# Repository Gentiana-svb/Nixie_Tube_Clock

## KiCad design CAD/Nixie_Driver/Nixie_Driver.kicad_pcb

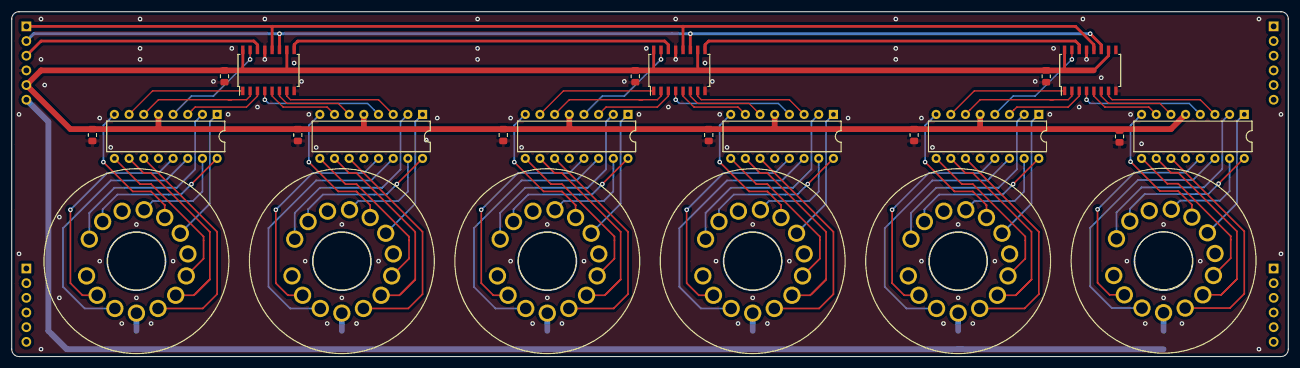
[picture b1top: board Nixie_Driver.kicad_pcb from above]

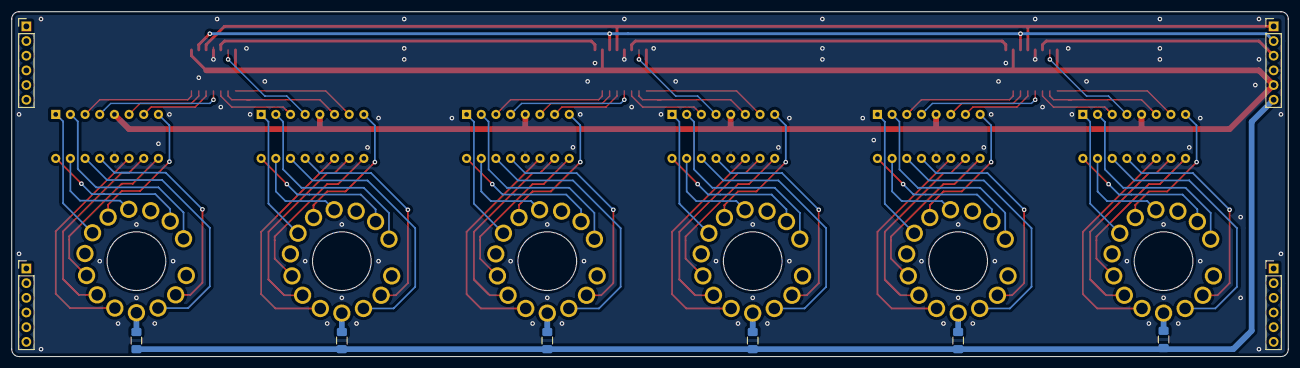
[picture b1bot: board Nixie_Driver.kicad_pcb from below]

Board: 2 copper layers, 221.0 x 59.7 mm, 34 parts (10 on the bottom side), 98 nets.

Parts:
C1, C2, C3, C4, C5, C6, C7, C8, C9: 0.1u; C_0805_2012Metric_Pad1.15x1.40mm_HandSolder
J1, J2, J3, J4: Conn_01x06; PinHeader_1x06_P2.54mm_Vertical
R1, R2, R3, R4, R5, R6: 10k; R_1206_3216Metric_Pad1.42x1.75mm_HandSolder
U1, U2, U3: 74HC595; SOIC-16W_5.3x10.2mm_P1.27mm
U4, U5, U6, U10, U11, U12: 74141; DIP-16_W7.62mm
U7, U8, U9, U13, U14, U15: IN-18

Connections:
+5V: C1.1, C2.1, C3.1, C4.1, C5.1, C6.1, C7.1, C8.1, C9.1, J1.5, U1.10, U1.16, U2.10, U2.16, U3.10, U3.16, U4.5, U5.5, U6.5, U10.5, U11.5, U12.5
+48V: J1.6, R1.1, R2.1, R3.1, R4.1, R5.1, R6.1
/HH1: U1.3, U4.3
/HH2: U1.2, U4.6
/HH4: U1.1, U4.7
/HH8: U1.15, U4.4
/HL1: U1.7, U5.3
/HL2: U1.6, U5.6
/HL4: U1.5, U5.7
/HL8: U1.4, U5.4
/MH1: U2.3, U6.3
/MH2: U2.2, U6.6
/MH4: U2.1, U6.7
/MH8: U2.15, U6.4
/ML1: U2.7, U10.3
/ML2: U2.6, U10.6
/ML4: U2.5, U10.7
/ML8: U2.4, U10.4
/RCK: J1.1, U1.12, U2.12, U3.12
/SCK: J1.2, U1.11, U2.11, U3.11
/SH1: U3.3, U11.3
/SH2: U3.2, U11.6
/SH4: U3.1, U11.7
/SH8: U3.15, U11.4
/SL1: U3.7, U12.3
/SL2: U3.6, U12.6
/SL4: U3.5, U12.7
/SL8: U3.4, U12.4
GND: C1.2, C2.2, C3.2, C4.2, C5.2, C6.2, C7.2, C8.2, C9.2, J1.4, U1.8, U1.13, U2.8, U2.13, U3.8, U3.13, U4.12, U5.12, U6.12, U10.12, U11.12, U12.12
unnamed: J1.3, U1.14
unnamed: R1.2, U7.4
unnamed: R2.2, U8.4
unnamed: R3.2, U9.4
unnamed: R4.2, U13.4
unnamed: R5.2, U14.4
unnamed: R6.2, U15.4
unnamed: U1.9, U2.14
unnamed: U2.9, U3.14
unnamed: U4.1, U7.9
unnamed: U4.2, U7.14
unnamed: U4.8, U7.10
unnamed: U4.9, U7.7
unnamed: U4.10, U7.6
unnamed: U4.11, U7.5
unnamed: U4.13, U7.2
unnamed: U4.14, U7.3
unnamed: U4.15, U7.11
unnamed: U4.16, U7.13
unnamed: U5.1, U8.9
unnamed: U5.2, U8.14
unnamed: U5.8, U8.10
unnamed: U5.9, U8.7
unnamed: U5.10, U8.6
unnamed: U5.11, U8.5
unnamed: U5.13, U8.2
unnamed: U5.14, U8.3
unnamed: U5.15, U8.11
unnamed: U5.16, U8.13
unnamed: U6.1, U9.9
unnamed: U6.2, U9.14
unnamed: U6.8, U9.10
unnamed: U6.9, U9.7
unnamed: U6.10, U9.6
unnamed: U6.11, U9.5
unnamed: U6.13, U9.2
unnamed: U6.14, U9.3
unnamed: U6.15, U9.11
unnamed: U6.16, U9.13
unnamed: U10.1, U13.9
unnamed: U10.2, U13.14
unnamed: U10.8, U13.10
unnamed: U10.9, U13.7
unnamed: U10.10, U13.6
unnamed: U10.11, U13.5
unnamed: U10.13, U13.2
unnamed: U10.14, U13.3
unnamed: U10.15, U13.11
unnamed: U10.16, U13.13
unnamed: U11.1, U14.9
unnamed: U11.2, U14.14
unnamed: U11.8, U14.10
unnamed: U11.9, U14.7
unnamed: U11.10, U14.6
unnamed: U11.11, U14.5
unnamed: U11.13, U14.2
unnamed: U11.14, U14.3
unnamed: U11.15, U14.11
unnamed: U11.16, U14.13
unnamed: U12.1, U15.9
unnamed: U12.2, U15.14
unnamed: U12.8, U15.10
unnamed: U12.9, U15.7
unnamed: U12.10, U15.6
unnamed: U12.11, U15.5
unnamed: U12.13, U15.2
unnamed: U12.14, U15.3
unnamed: U12.15, U15.11
unnamed: U12.16, U15.13

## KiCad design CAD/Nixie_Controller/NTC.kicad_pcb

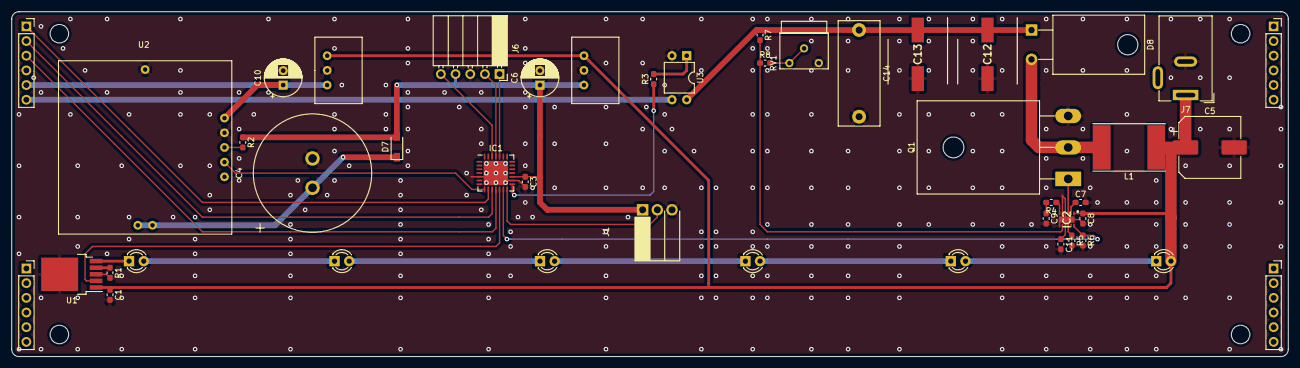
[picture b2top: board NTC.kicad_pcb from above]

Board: 2 copper layers, 221.0 x 59.7 mm, 46 parts (0 on the bottom side), 36 nets.

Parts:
C1, C3: 0.1u; C_0603_1608Metric_Pad1.05x0.95mm_HandSolder
C4: 1.5F; EDLC
C5: 100u; CP_Elec_10x10.5
C6, C10: 100u; CP_Radial_D6.3mm_P2.50mm
C7: 1u; C_0603_1608Metric_Pad1.05x0.95mm_HandSolder
C8: 10u; C_0603_1608Metric_Pad1.05x0.95mm_HandSolder
C9: 0.022u; C_0603_1608Metric_Pad1.05x0.95mm_HandSolder
C11: 0.22u; C_0603_1608Metric_Pad1.05x0.95mm_HandSolder
C12, C13: ULR2G8R2MNL1GS; CAPAE1030X1100N
C14: 0.1u; C_Rect_L18.0mm_W7.0mm_P15.00mm_FKS3_FKP3
D1, D2, D3, D4, D5, D6: LED; LED_D3.0mm_Clear
D7: SS2040FL; SOD-123FL
D8: SCS206AG; TO-220-2_Horizontal_TabDown
IC1: PIC18F27Q10T-I_ML; QFN-28-1EP_6x6mm_P0.65mm_EP4.25x4.25mm
IC2: LM51551DSSR; SON50P200X300X80-13N
J1: SB412A
J2, J3, J4, J5: Conn_01x06; PinSocket_1x06_P2.54mm_Vertical
J6: ICSP; PinSocket_1x05_P2.54mm_Horizontal
J7: Barrel_Jack_Switch; BarrelJack_Wuerth_6941xx301002
L1: 22u; L_Taiyo-Yuden_NR-80xx_HandSoldering
Q1: TK31N60X; TO-247-3_Horizontal_TabDown
R1: 20; R_0603_1608Metric_Pad1.05x0.95mm_HandSolder
R2, R6, R8: 10k; R_0603_1608Metric_Pad1.05x0.95mm_HandSolder
R3: 300; R_0603_1608Metric_Pad1.05x0.95mm_HandSolder
R4: 12k; R_0603_1608Metric_Pad1.05x0.95mm_HandSolder
R5: 43k; R_0603_1608Metric_Pad1.05x0.95mm_HandSolder
R7: 2M; R_0603_1608Metric_Pad1.05x0.95mm_HandSolder
RV1: 4.7k; Potentiometer_Bourns_3339W_Horizontal
U1: NJW4617; TO-252-5_TabPin3
U2: AE-GPS
U3: TLP627; DIP-4_W7.62mm
U4: M78AR033-1; M78AR-1
U5: M78AR05-1; M78AR-1

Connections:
+3V3: C3.1, C6.1, D7.2, IC1.17, J1.1, J6.4, R2.1, U4.3
+5V: C10.1, J5.5, U2.1, U5.3
+24V: C1.1, C5.1, C8.1, D1.2, IC2.1, J7.1, L1.1, U1.1, U4.1, U5.1
+200V: C12.1, C13.1, C14.1, D8.1, R7.1, U3.4
/BRT: IC1.15, R3.1
/HV: J5.6, U3.3
/LED: IC1.12, U1.2
/MCLR: IC1.26, J6.5
/PGC: IC1.24, J6.1
/PGD: IC1.25, J6.2
/Pyro: IC1.14, J1.2
/RCK: IC1.9, J5.1
/RX: IC1.8, U2.4
/SCK: IC1.10, J5.2
/SER: IC1.11, J5.3
/power/GATE: IC2.3, Q1.1
EN: IC1.13, IC2.12, R6.1
GND: C1.2, C3.2, C4.2, C5.2, C6.2, C7.2, C8.2, C9.2, C10.2, C11.2, C12.2, C13.2, C14.2, IC1.5, IC1.16, IC1.29, IC2.4, IC2.5, IC2.7, IC2.13, J1.3, J5.4, J6.3, J7.2, Q1.3, R1.2, R5.2, R6.2, RV1.3, U1.3, U2.2, U2.8, U3.2, U4.2, U5.2
unnamed: C4.1, D7.1, U2.6, U2.7
unnamed: C7.1, IC2.2
unnamed: C9.1, R4.2
unnamed: C11.1, IC2.9
unnamed: D1.1, D2.2
unnamed: D2.1, D3.2
unnamed: D3.1, D4.2
unnamed: D4.1, D5.2
unnamed: D5.1, D6.2
unnamed: D6.1, U1.5
unnamed: D8.2, L1.2, Q1.2
unnamed: IC2.6, R4.1
unnamed: IC2.8, R7.2, R8.1
unnamed: IC2.10, R5.1
unnamed: R1.1, U1.4
unnamed: R2.2, U2.3
unnamed: R3.2, U3.1
unnamed: R8.2, RV1.1, RV1.2

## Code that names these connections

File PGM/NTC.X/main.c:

// Nixie Tube Clock Controll Program
// MCU      : PIC18F27Q10
// Compiler : XC8 v2.32
// Date     : 3/27/2021

#include "config.h"
#include "library/UART/UART.h"
#include <stdint.h>
#include <string.h>
#include <xc.h>

// PORT Define
#define RX   RC0
#define RCK  LATC1
#define SCK  LATC2
#define SI   LATC3
#define LED  LATC4
#define EN   LATC5
#define PYRO RC6
#define BRT  LATC7

// DGM Effect
#define DGM_TIME  3.5 // sec
#define DGM_START (DGM_TIME * 100) / 5
#define DGM_INT   (100 - DGM_START) / 5

// Global
_Bool g_t0_f;
_Bool dgm_f;
uint32_t g_time;

// RTC Receive
void RTC_Read(uint8_t data);

// Data Conversion
uint32_t Convert_data(uint32_t data);
uint32_t DGM_Effect(uint32_t time, uint8_t val);

// Device Control
void NTC_Write(uint32_t data);
void Duty_Control();
void IC595_Write(uint24_t data);

// Peripheral Control
void Set_PWM_Duty(uint8_t ch, int16_t duty);
_Bool T0_int(int16_t val);
_Bool T0_int2(int16_t val);

// Initialize
void init()
{
    // OSC
    OSCCON1 = 0x60;
    OSCFRQ = 0x08;

    // I/O
    TRISA = 0x00;
    TRISB = 0x00;
    TRISC = 0x41;

    // A/D
    ANSELA = 0x00;
    ANSELB = 0x00;
    ANSELC = 0x00;

    // Timer0
    T0CON0 = 0x90;
    T0CON1 = 0xd0; // 500kHz
    TMR0IE = 1;

    // Timer2
    T2CLKCON = 0x01; // Clock source is Fosc/4
    T2PR = 0xfe;     // Maximum Duty Resolution
    T2CON = 0xf0;    // Timer2 enable, Pre scaler 1:128, Post scaler 1:1

    // PWM3
    PWM3CON = 0x80;            // PWM enable
    CCPTMRSbits.P3TSEL = 0x01; // PWM3 based Timer2
    Set_PWM_Duty(3, 0);

    // PWM4
    PWM4CON = 0x80;            // PWM enable
    CCPTMRSbits.P4TSEL = 0x01; // PWM4 based Timer2
    Set_PWM_Duty(4, 0);

    // PPS unlock
    PPSLOCK = 0x55;
    PPSLOCK = 0xAA;
    PPSLOCK = 0x00;

    // PPS
    RX1PPS = 0x10; // RC0 = RX1
    RC4PPS = 0x07; // RC4 = PWM3
    RC7PPS = 0x08; // RC7 = PWM4

    // PPS lock
    PPSLOCK = 0x55;
    PPSLOCK = 0xAA;
    PPSLOCK = 0x00;

    // Interrupts
    ei();
    PEIE = 1;

    // UART
    UART_Init(9600);
}

// Main
void main()
{
    uint8_t cnt = 0;
    uint8_t val = 0;

    init();

    while (1) {
        if (T0_int(2)) {
            Duty_Control();
        }

        if (EN) {
            if (T0_int2(50)) {
                if (dgm_f) {
                    cnt++;

                    if (cnt < DGM_START) {
                        val = 6;
                    }
                    else if (cnt < (DGM_START + DGM_INT * 1)) {
                        val = 5;
                    }
                    else if (cnt < (DGM_START + DGM_INT * 2)) {
                        val = 4;
                    }
                    else if (cnt < (DGM_START + DGM_INT * 3)) {
                        val = 3;
                    }
                    else if (cnt < (DGM_START + DGM_INT * 4)) {
                        val = 2;
                    }
                    else if (cnt < (DGM_START + DGM_INT * 5)) {
                        val = 1;
                    }
                    else {
                        val = 0;
                        dgm_f = 0;
                        cnt = 0;
                    }

                    NTC_Write(DGM_Effect(g_time, val));
                }
                else {
                    NTC_Write(g_time);
                }
            }
        }
        else {
            if (dgm_f) {
                dgm_f = 0;
            }
        }
    }
}

// Interupts
void __interrupt() isr()
{
    // 1ms Interrupt
    if (TMR0IF) {
        WRITETIMER0(65036);
        TMR0IF = 0;
        g_t0_f = ~g_t0_f;
    }

    if (RCIF) {
        RTC_Read(UART_Read());
    }
}

// Nixie Tube Output
void NTC_Write(uint32_t data)
{
    uint8_t buff[6]; // [0][1][2][3][4][5]
    uint24_t temp = 0;

    if (data > 999999) {
        data %= 1000000;
    }

    buff[5] = (data / 1) % 10;
    buff[4] = (data / 10) % 10;
    buff[3] = (data / 100) % 10;
    buff[2] = (data / 1000) % 10;
    buff[1] = (data / 10000) % 10;
    buff[0] = (data / 100000) % 10;

    temp |= ((uint24_t)buff[5] << 0);
    temp |= ((uint24_t)buff[4] << 4);
    temp |= ((uint24_t)buff[3] << 8);
    temp |= ((uint24_t)buff[2] << 12);
    temp |= ((uint24_t)buff[1] << 16);
    temp |= ((uint24_t)buff[0] << 20);

    IC595_Write(temp);
}

// Every Brightness Control
void Duty_Control()
{
    static uint16_t led = 0;
    static uint16_t ntc = 0;

    const uint16_t led_limit = 0x0100;
    const uint16_t ntc_limit = 0x03ff;

    if (PYRO) {
        EN = 1;

        if (led < led_limit) {
            led++;
        }
        if (ntc < ntc_limit) {
            ntc++;
        }
    }
    else {
        if (ntc > 0) {
            ntc--;
            if (ntc == 0) {
                EN = 0;
            }
        }
        if (led > 0) {
            led--;
        }
    }

    Set_PWM_Duty(3, led);
    Set_PWM_Duty(4, ntc);
}

// RTC Receive
void RTC_Read(uint8_t data)
{
    static int16_t cnt = 0;
    static char str[10];

    switch (cnt) {
        case 0:
            // Receive Start
            if (data == '$') {
                // Buffer Clear
                memset(str, '\0', sizeof(str));
                cnt++;
            }
            break;

        case 3:
            // NMEA ZDA Format
            if (data == 'Z') {
                cnt++;
            }
            else {
                cnt = 0;
            }
            break;

        case 7:
        case 8:
        case 9:
        case 10:
        case 11:
        case 12:
            str[cnt - 7] = data;
            cnt++;
            break;

        default:
            cnt++;
            break;
    }

    // Receive Complete
    if (cnt >= 13) {
        g_time = Convert_data(atol(str));
        cnt = 0;
    }
}

// UTC to JST
uint32_t Convert_data(uint32_t data)
{
    uint32_t hour;
    uint32_t min;
    uint32_t sec;

    hour = (data / 10000) % 100;
    min = (data / 100) % 100;
    sec = (data / 1) % 100;

    // UTC Convert to JST
    hour = (hour + 9) % 24;

    // Check_Divergence
    if ((((min + 1) % 15) == 0) && (sec >= 55)) {
        dgm_f = 1;

        if (min == 59) {
            hour = (++hour) % 24;
        }

        min = (++min) % 60;
        sec = 0;
    }

    return (hour * 10000) + (min * 100) + (sec * 1);
}

// Data Randomize
uint32_t DGM_Effect(uint32_t time, uint8_t val)
{
    uint32_t data;
    static const uint32_t factor[7] = { 1, 10, 100, 1000, 10000, 100000, 1000000 };

    if (val >= 6) {
        val = 6;
    }

    time /= factor[val];
    data = (uint32_t)rand() * 1000 + rand();
    data %= factor[val];
    data += time * factor[val];

    return data;
}

// 74HC595 Data Write
void IC595_Write(uint24_t data)
{
    int16_t i;

    for (i = 0; i < 24; i++) {
        SI = (((data >> i) & 0x01) != 0);
        SCK = 0;
        SCK = 1;
    }

    RCK = 0;
    RCK = 1;
}

// PWM Module Control
void Set_PWM_Duty(uint8_t ch, int16_t duty)
{
    switch (ch) {
        case 3:
            PWM3DCH = duty >> 2;
            PWM3DCL = duty;
            break;

        case 4:
            PWM4DCH = duty >> 2;
            PWM4DCL = duty;
            break;

        default:
            return;
    }
}

// Timer0 Custom Interval
_Bool T0_int(int16_t val)
{
    static uint8_t flag = 0;
    static int16_t cnt = 0;

    if (flag != g_t0_f) {
        flag = g_t0_f;
        cnt++;
        if (cnt >= val) {
            cnt = 0;
            return 1;
        }
    }

    return 0;
}

// Timer0 Custom Interval 2
_Bool T0_int2(int16_t val)
{
    static uint8_t flag = 0;
    static int16_t cnt = 0;

    if (flag != g_t0_f) {
        flag = g_t0_f;
        cnt++;
        if (cnt >= val) {
            cnt = 0;
            return 1;
        }
    }

    return 0;
}

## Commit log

2021-04-23 Separate PGM
2021-10-29 add library
